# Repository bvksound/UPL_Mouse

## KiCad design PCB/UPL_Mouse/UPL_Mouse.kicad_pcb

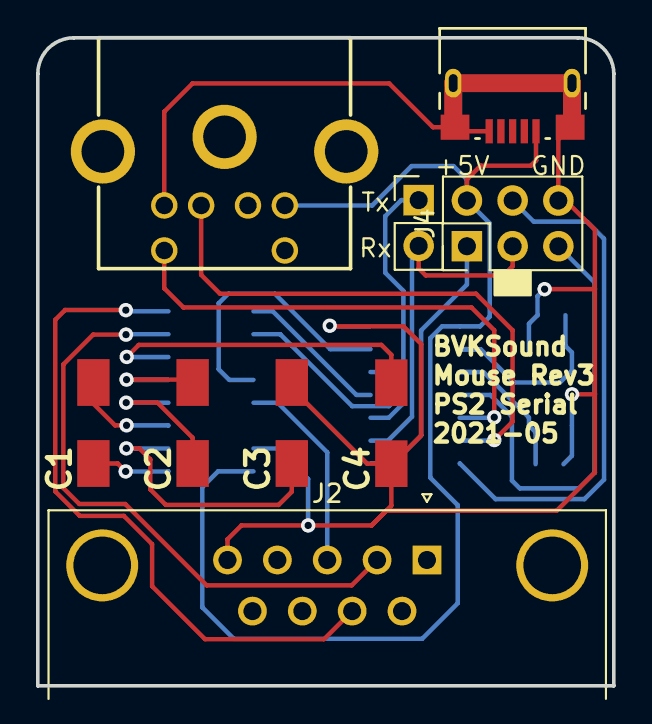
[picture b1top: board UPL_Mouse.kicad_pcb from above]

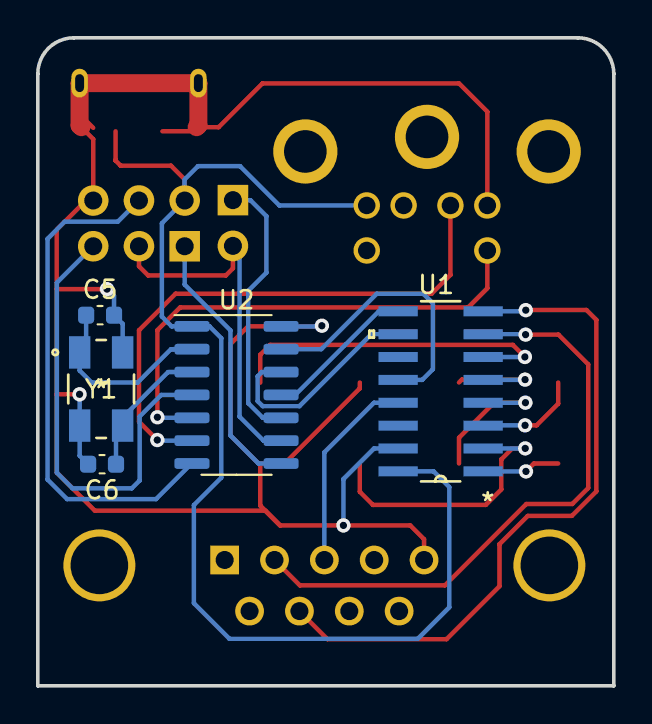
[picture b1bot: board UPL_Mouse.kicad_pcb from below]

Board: 2 copper layers, 32.0 x 36.0 mm, 14 parts (6 on the bottom side), 23 nets.

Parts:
C1, C2, C3, C4: EEE-FC1V1R0R; CAPAE430X550N
C5, C6: 22nF; C_0603_1608Metric
J1: PS2_5749180-1; 5749180-1
J2: DB9_Female; DSUB-9_Female_Horizontal_P2.77x2.84mm_EdgePinOffset4.94mm_H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
J3: USB Micro_10118193-0001LF; 10118193-0001LF
J4: AVR-ISP-6; PinHeader_2x03_P2.54mm_Vertical
J5: Conn_01x02_Male; PinHeader_1x02_P2.54mm_Vertical
U1: MAX232DR
U2: ATtiny84-20SSU; SOIC-14_3.9x8.7mm_P1.27mm
Y1: ABM3B-20.000MHZ

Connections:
GND: C3.2, C4.1, C5.2, C6.2, J1.3, J2.5, J3.5, J4.6, U1.15, U2.14, Y1.2, Y1.4
unnamed: C1.1, U1.1
unnamed: C1.2, U1.3
unnamed: C2.1, U1.4
unnamed: C2.2, U1.5
unnamed: C3.1, U1.2
unnamed: C4.2, U1.6
unnamed: C5.1, U2.2, Y1.1
unnamed: C6.1, U2.3, Y1.3
unnamed: J1.1, U2.6
unnamed: J1.5, U2.5
unnamed: J2.2, U1.7
unnamed: J2.3, U1.13
unnamed: J2.7, U1.8
unnamed: J4.1, U2.8
unnamed: J4.3, J5.2, U2.9
unnamed: J4.4, U2.7
unnamed: J4.5, U2.4
unnamed: J5.1, U2.10
unnamed: U1.9, U2.11
unnamed: U1.10, U2.12
unnamed: U1.12, U2.13
VCC: J1.4, J3.1, J4.2, U1.16, U2.1

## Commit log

2021-03-06 Sandbox code
2021-03-27 draft ps2 code added
    example ps2 code added
2021-03-28 Rev 1 design finished
2021-04-11 Update Design and Code
    Update in code regarding configuration of the chip.
    Update in PCB due to wrong footprint mini din connector.
2021-05-06 Update ps2serial.ino
    porting to attiny84
2021-05-07 update with attiny84
    update with attiny84 and rx tx
2021-05-08 gerber files and cleanup pcb
2021-05-22 first release
2021-12-31 Minor debugging update
2023-02-03 cleanup

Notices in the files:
parts and their libraries:
Copyright 2016 Accelerated Designs. All rights reserved.
